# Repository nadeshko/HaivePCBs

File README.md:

# HaivePCBs

3 Version of Top PCBs; Top, General and Falcon. The Top PCBs have SM LEDs to determine the container number and unique code

The Front PCB directly connects the road with the container to provide power and ground

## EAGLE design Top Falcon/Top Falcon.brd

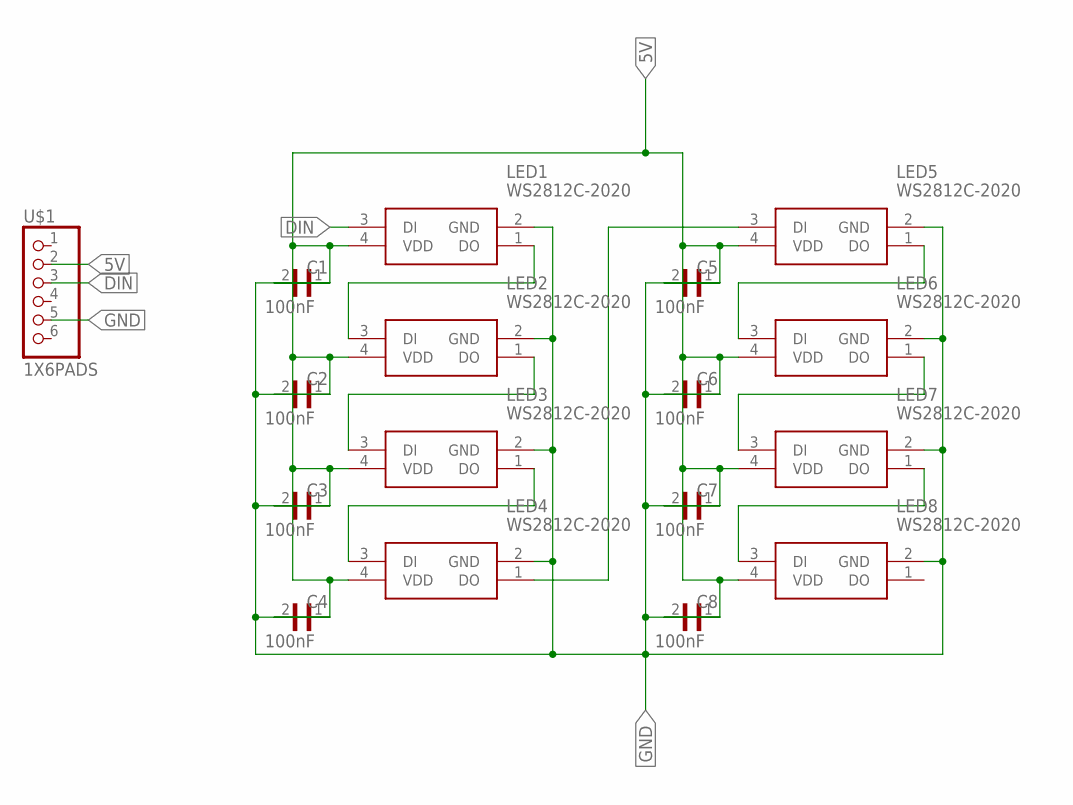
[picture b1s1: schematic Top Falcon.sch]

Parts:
C1, C2, C3, C4, C5, C6, C7, C8: 100nF; CAPC1005X55N
LED1, LED2, LED3, LED4, LED5, LED6, LED7, LED8: WS2812C-2020; WS2812C2020
U$1: 1X6PADS

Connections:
5V: C1.2, C2.2, C3.2, C4.2, C5.2, C6.2, C7.2, C8.2, LED1.4 (VDD), LED2.4 (VDD), LED3.4 (VDD), LED4.4 (VDD), LED5.4 (VDD), LED6.4 (VDD), LED7.4 (VDD), LED8.4 (VDD), U$1.2
DIN: LED1.3 (DI), U$1.3
GND: C1.1, C2.1, C3.1, C4.1, C5.1, C6.1, C7.1, C8.1, LED1.2 (GND), LED2.2 (GND), LED3.2 (GND), LED4.2 (GND), LED5.2 (GND), LED6.2 (GND), LED7.2 (GND), LED8.2 (GND), U$1.5
unnamed: LED1.1 (DO), LED2.3 (DI)
unnamed: LED2.1 (DO), LED3.3 (DI)
unnamed: LED3.1 (DO), LED4.3 (DI)
unnamed: LED4.1 (DO), LED5.3 (DI)
unnamed: LED5.1 (DO), LED6.3 (DI)
unnamed: LED6.1 (DO), LED7.3 (DI)
unnamed: LED7.1 (DO), LED8.3 (DI)

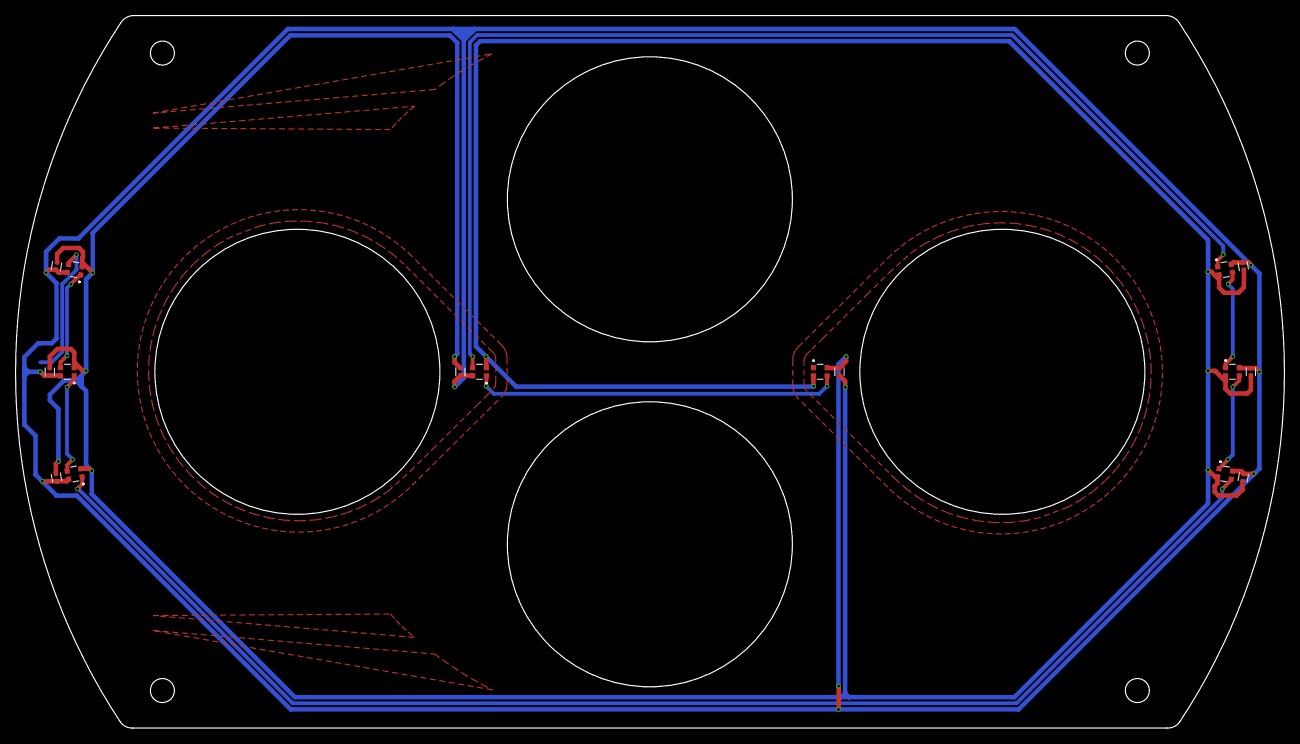
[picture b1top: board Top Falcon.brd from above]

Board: 2 copper layers, 169.2 x 95.0 mm, 17 parts (1 on the bottom side), 10 nets.

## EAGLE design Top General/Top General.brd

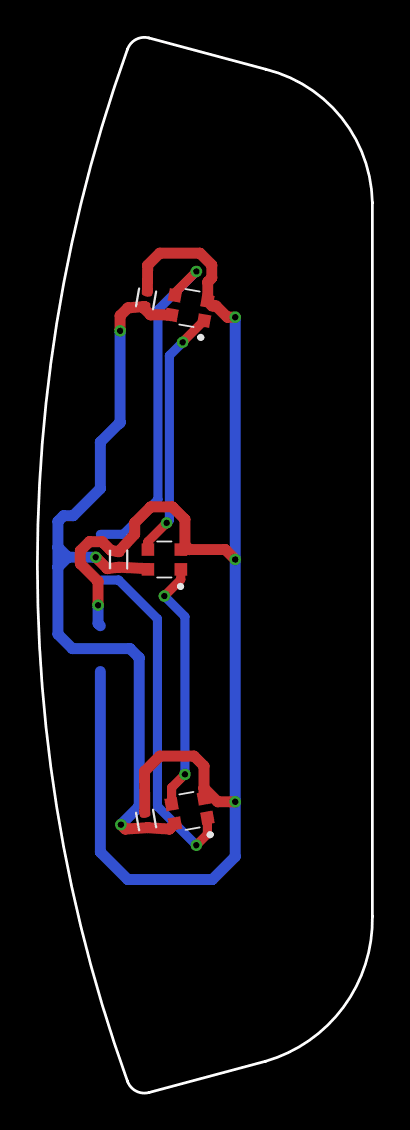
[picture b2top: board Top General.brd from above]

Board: 2 copper layers, 18.6 x 58.7 mm, 7 parts (1 on the bottom side), 6 nets.

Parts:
C1, C2, C3: 0.1uF; CAPC1005X55N-BACKUP
LED1, LED2, LED3: WS2812C-2020; WS2812C2020
SMDPADS: 1X6PADS

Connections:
5V: C1.2, C2.2, C3.2, LED1.4, LED2.4, LED3.4, SMDPADS.1, SMDPADS.2
DIN: LED1.3, SMDPADS.3
DOUT: LED3.1, SMDPADS.4
GND: C1.1, C2.1, C3.1, LED1.2, LED2.2, LED3.2, SMDPADS.5, SMDPADS.6
unnamed: LED1.1, LED2.3
unnamed: LED2.1, LED3.3
